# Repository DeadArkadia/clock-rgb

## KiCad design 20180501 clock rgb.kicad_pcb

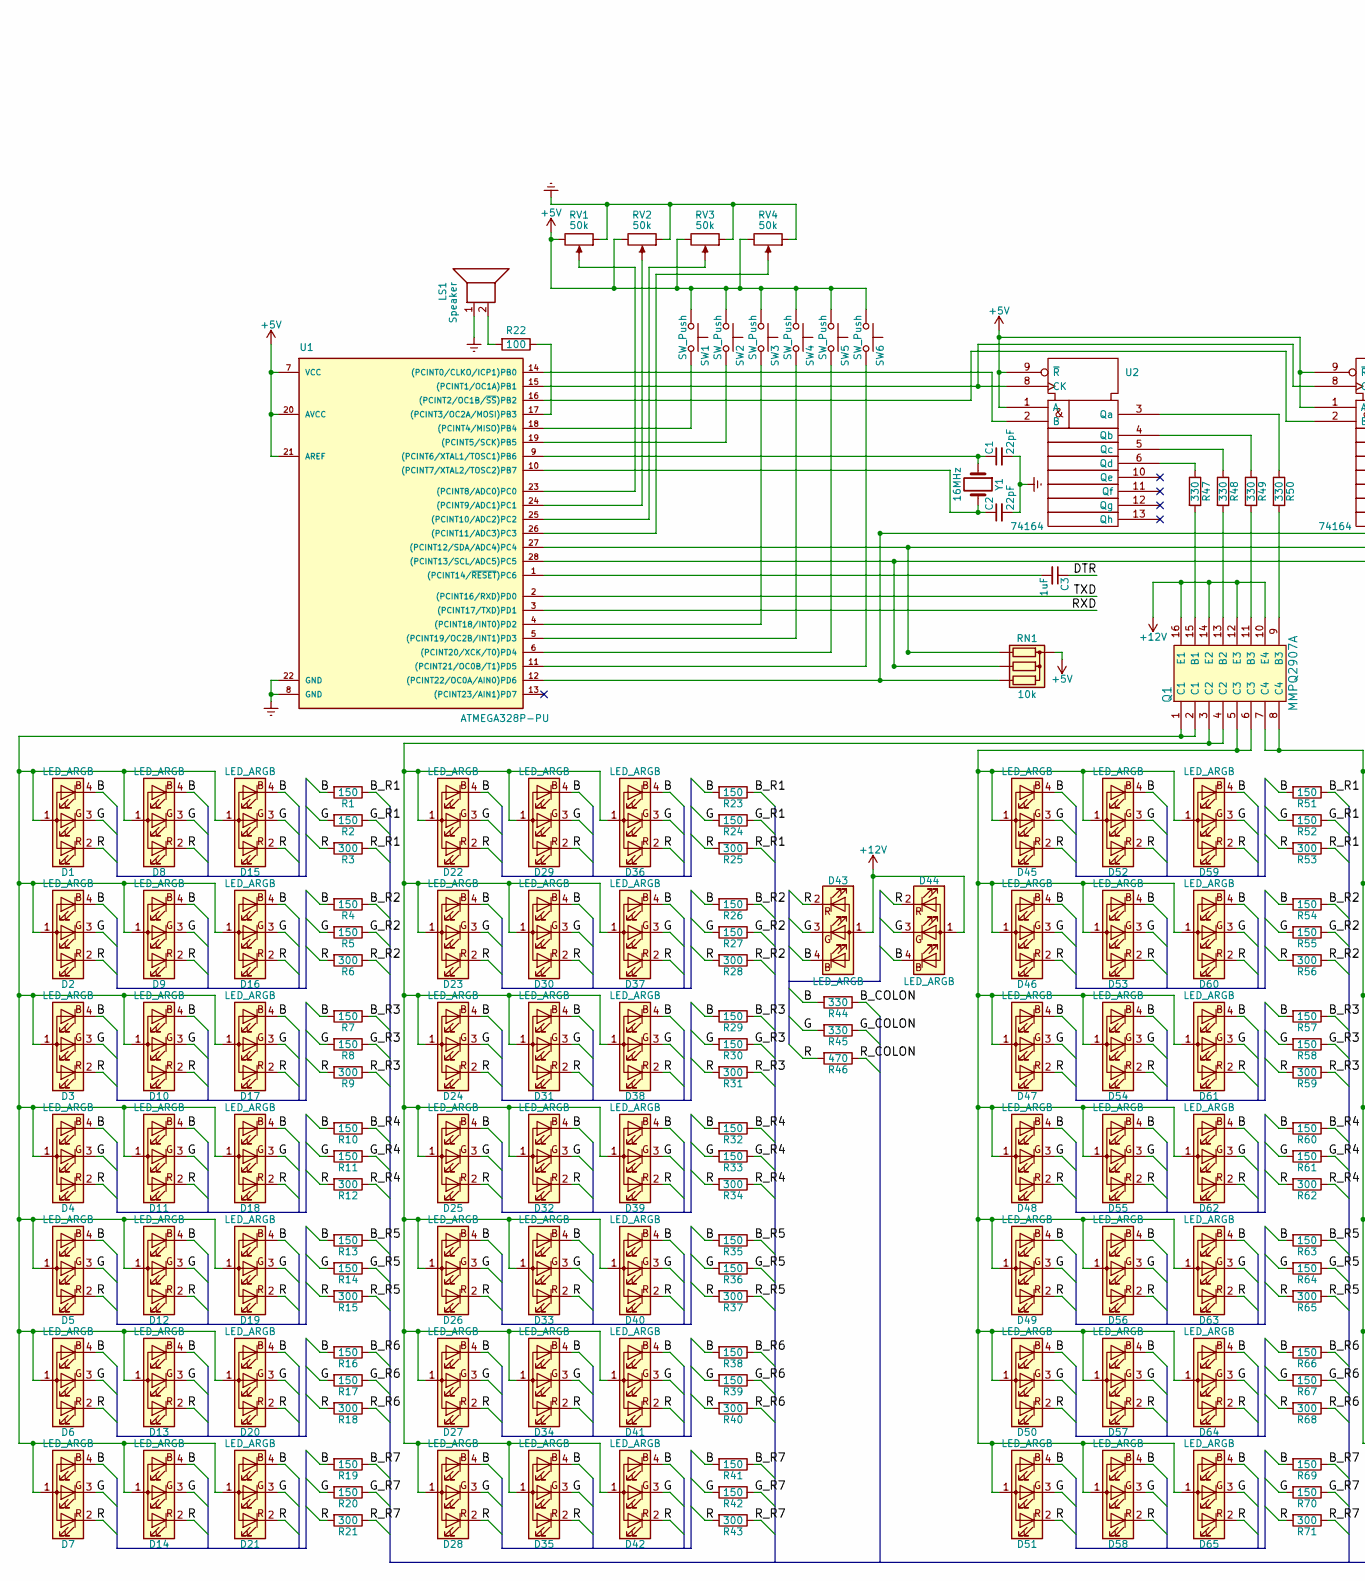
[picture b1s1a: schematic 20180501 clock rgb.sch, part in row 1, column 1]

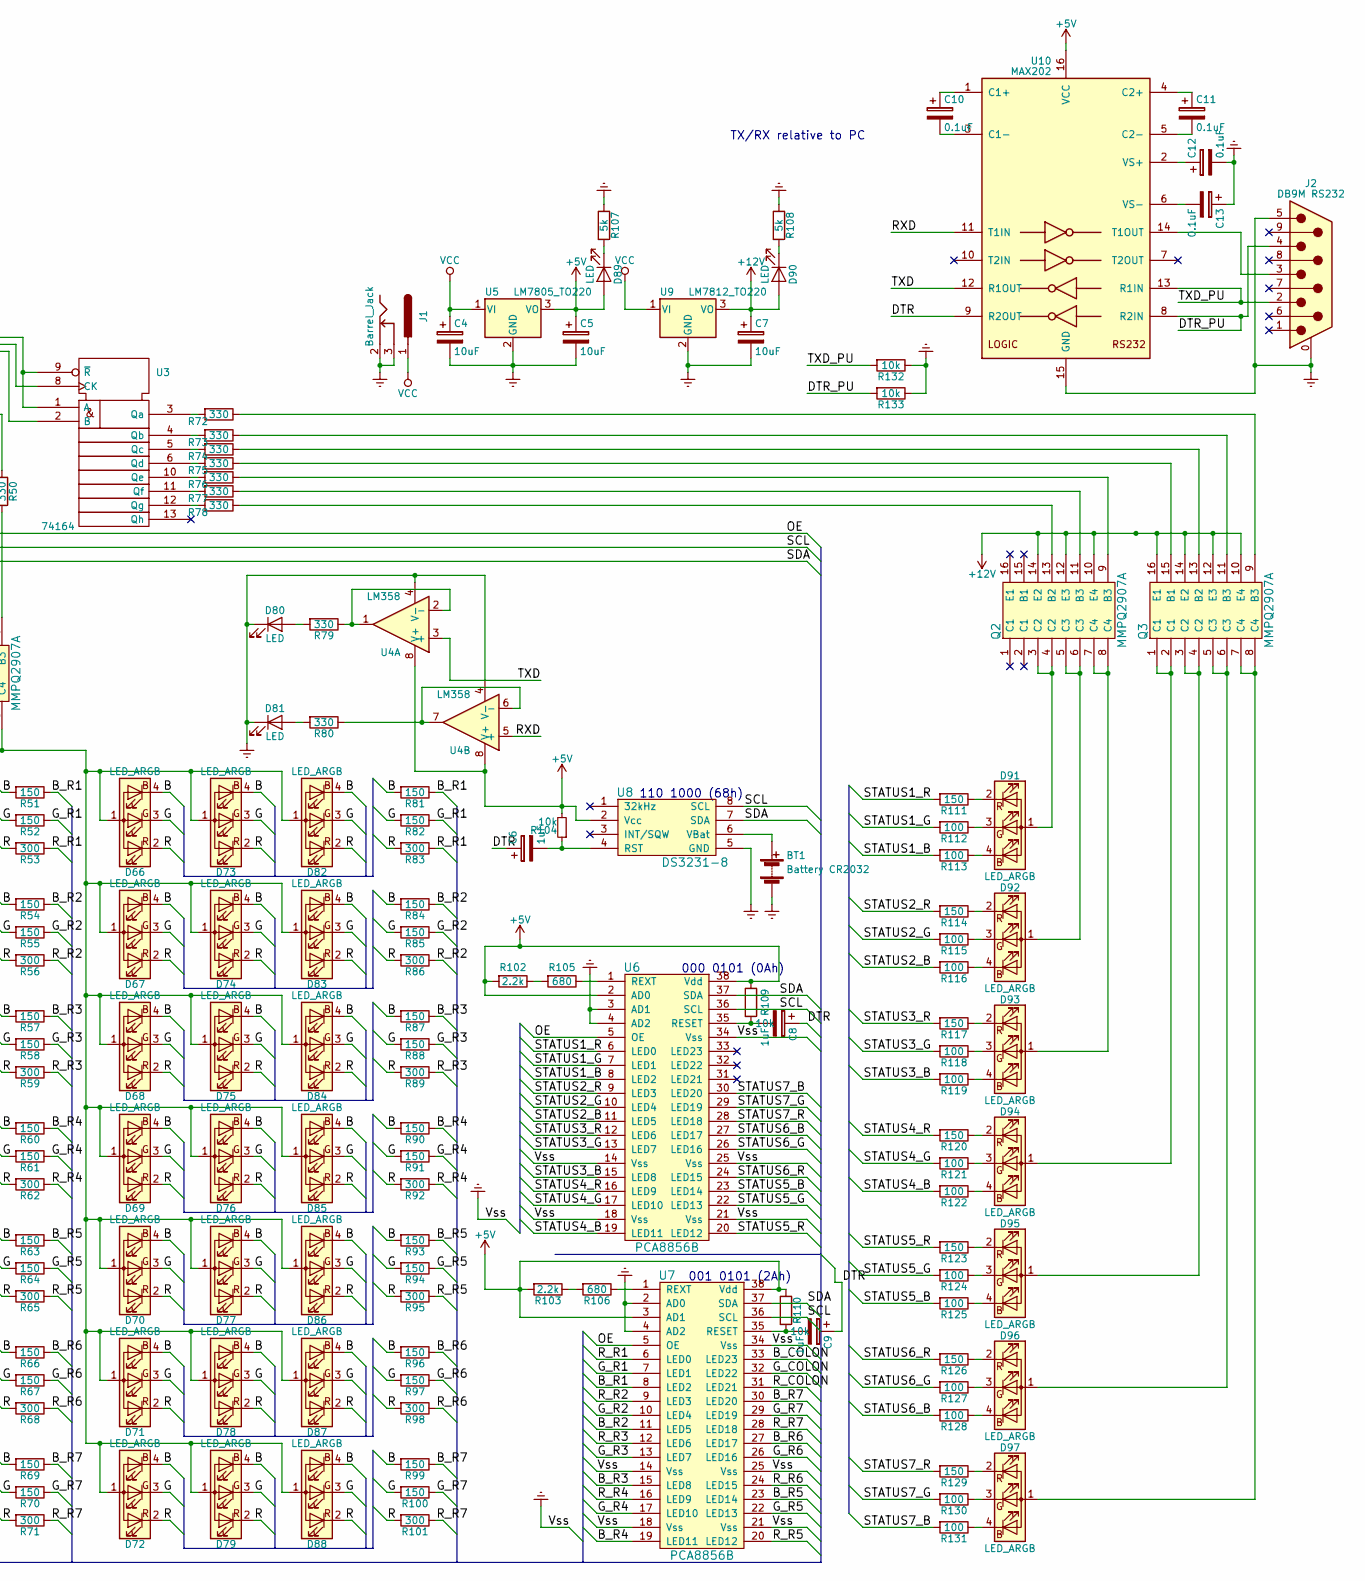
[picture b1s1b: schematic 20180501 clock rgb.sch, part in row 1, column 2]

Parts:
BT1: Battery CR2032; BatteryHolder_Keystone_1058_1x2032
C1, C2: 22pF; C_Rect_L4.0mm_W2.5mm_P2.50mm
C3: 1uF; C_Rect_L4.0mm_W2.5mm_P2.50mm
C4, C5, C7: 10uF; CP_Radial_D5.0mm_P2.50mm
C6, C8, C9: 1uF; CP_Radial_D5.0mm_P2.50mm
C10, C11, C12, C13: 0.1uF; CP_Radial_D5.0mm_P2.50mm
D1, D2, D3, D4, D5, D6, D7, D8, D9, D10, D11, D12, D13, D14, D15, D16, D17, D18, D19, D20, D21, D22, D23, D24, D25, D26, D27, D28, D29, D30, D31, D32, D33, D34, D35, D36, D37, D38, D39, D40, D41, D42, D43, D44, D45, D46, D47, D48, D49, D50, D51, D52, D53, D54, D55, D56, D57, D58, D59, D60, D61, D62, D63, D64, D65, D66, D67, D68, D69, D70, D71, D72, D73, D74, D75, D76, D77, D78, D79, D82, D83, D84, D85, D86, D87, D88, D91, D92, D93, D94, D95, D96, D97: LED_ARGB; LED_SK6812MINI_PLCC4_3.5x3.5mm_P1.75mm
D80, D81, D89, D90: LED; LED_D5.0mm
J1: Barrel_Jack; BARREL_JACK
J2: DB9M RS232; DSUB-9_Male_Horizontal_P2.77x2.84mm_EdgePinOffset7.70mm_Hou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
LS1: Speaker; Buzzer_15x7.5RM7.6
Q1, Q2, Q3: MMPQ2907A; SOIC-16_3.9x9.9mm_Pitch1.27mm
R1, R2, R4, R5, R7, R8, R10, R11, R13, R14, R16, R17, R19, R20, R23, R24, R26, R27, R29, R30, R32, R33, R35, R36, R38, R39, R41, R42, R51, R52, R54, R55, R57, R58, R60, R61, R63, R64, R66, R67, R69, R70, R81, R82, R84, R85, R87, R88, R90, R91, R93, R94, R96, R97, R99, R100, R111, R114, R117, R120, R123, R126, R129: 150; R_1210_3225Metric_Pad1.39x2.70mm_HandSolder
R3, R6, R9, R12, R15, R18, R21, R25, R28, R31, R34, R37, R40, R43, R53, R56, R59, R62, R65, R68, R71, R83, R86, R89, R92, R95, R98, R101: 300; R_1210_3225Metric_Pad1.39x2.70mm_HandSolder
R22: 100; R_Axial_DIN0207_L6.3mm_D2.5mm_P10.16mm_Horizontal
R44, R45, R47, R48, R49, R50, R72, R73, R74, R75, R76, R77, R78, R79, R80: 330; R_1210_3225Metric_Pad1.39x2.70mm_HandSolder
R46: 470; R_1210_3225Metric_Pad1.39x2.70mm_HandSolder
R102, R103: 2.2k; R_Axial_DIN0207_L6.3mm_D2.5mm_P10.16mm_Horizontal
R104: 10k; R_Axial_DIN0207_L6.3mm_D2.5mm_P10.16mm_Horizontal
R105, R106: 680; R_Axial_DIN0207_L6.3mm_D2.5mm_P10.16mm_Horizontal
R107, R108: 5k; R_Axial_DIN0207_L6.3mm_D2.5mm_P10.16mm_Horizontal
R109, R110, R132, R133: 10k; R_1210_3225Metric_Pad1.39x2.70mm_HandSolder
R112, R113, R115, R116, R118, R119, R121, R122, R124, R125, R127, R128, R130, R131: 100; R_1210_3225Metric_Pad1.39x2.70mm_HandSolder
RN1: 10k; R_Array_SIP4
RV1, RV2, RV3, RV4: 50k; Potentiometer_Alps_RK09K_Single_Vertical
SW1, SW2, SW3, SW4, SW5, SW6: SW_Push; SW_PUSH_6mm
U1: ATMEGA328P-PU; DIP-28_W7.62mm
U2, U3: 74164; DIP-14_W7.62mm
U4: LM358; SOIC-8_3.9x4.9mm_Pitch1.27mm
U5: LM7805_TO220; TO-220-3_Horizontal
U6, U7: PCA8856B; TSSOP-38_4.4x9.7mm_Pitch0.5mm
U8: DS3231-8; SOIC-8_3.9x4.9mm_Pitch1.27mm
U9: LM7812_TO220; TO-220-3_Horizontal
U10: MAX202; SOIC-16_3.9x9.9mm_Pitch1.27mm
Y1: 16MHz; Crystal_HC49-4H_Vertical

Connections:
+5V: C5.1, D89.2 (A), R102.2, R103.2, R104.2, R109.1, R110.1, RN1.1 (common), RV1.3, RV2.3, RV3.3, RV4.3, SW1.1, SW2.1, SW3.1, SW4.1, SW5.1, SW6.1, U1.7 (VCC), U1.20 (AVCC), U1.21 (AREF), U2.1 (A), U2.9 (~R), U3.1 (A), U3.9 (~R), U4.8 (V+), U5.3 (VO), U6.2 (AD0), U6.38 (Vdd), U7.3 (AD1), U7.38 (Vdd), U8.2 (Vcc), U10.16 (VCC)
+12V: C7.1, D43.1 (A), D44.1 (A), D90.2 (A), Q1.10 (E4), Q1.12 (E3), Q1.14 (E2), Q1.16 (E1), Q2.10 (E4), Q2.12 (E3), Q2.14 (E2), Q3.10 (E4), Q3.12 (E3), Q3.14 (E2), Q3.16 (E1), U9.3 (VO)
/B: D1.4 (BK), D2.4 (BK), D3.4 (BK), D4.4 (BK), D5.4 (BK), D6.4 (BK), D7.4 (BK), D8.4 (BK), D9.4 (BK), D10.4 (BK), D11.4 (BK), D12.4 (BK), D13.4 (BK), D14.4 (BK), D15.4 (BK), D16.4 (BK), D17.4 (BK), D18.4 (BK), D19.4 (BK), D20.4 (BK), D21.4 (BK), D22.4 (BK), D23.4 (BK), D24.4 (BK), D25.4 (BK), D26.4 (BK), D27.4 (BK), D28.4 (BK), D29.4 (BK), D30.4 (BK), D31.4 (BK), D32.4 (BK), D33.4 (BK), D34.4 (BK), D35.4 (BK), D36.4 (BK), D37.4 (BK), D38.4 (BK), D39.4 (BK), D40.4 (BK), D41.4 (BK), D42.4 (BK), D43.4 (BK), D44.4 (BK), D45.4 (BK), D46.4 (BK), D47.4 (BK), D48.4 (BK), D49.4 (BK), D50.4 (BK), D51.4 (BK), D52.4 (BK), D53.4 (BK), D54.4 (BK), D55.4 (BK), D56.4 (BK), D57.4 (BK), D58.4 (BK), D59.4 (BK), D60.4 (BK), D61.4 (BK), D62.4 (BK), D63.4 (BK), D64.4 (BK), D65.4 (BK), D66.4 (BK), D67.4 (BK), D68.4 (BK), D69.4 (BK), D70.4 (BK), D71.4 (BK), D72.4 (BK), D73.4 (BK), D74.4 (BK), D75.4 (BK), D76.4 (BK), D77.4 (BK), D78.4 (BK), D79.4 (BK), D82.4 (BK), D83.4 (BK), D84.4 (BK), D85.4 (BK), D86.4 (BK), D87.4 (BK), D88.4 (BK), R1.2, R4.2, R7.2, R10.2, R13.2, R16.2, R19.2, R23.2, R26.2, R29.2, R32.2, R35.2, R38.2, R41.2, R44.2, R51.2, R54.2, R57.2, R60.2, R63.2, R66.2, R69.2, R81.2, R84.2, R87.2, R90.2, R93.2, R96.2, R99.2
/B_COLON: R44.1, U7.33 (LED23)
/B_R1: R1.1, R23.1, R51.1, R81.1, U7.8 (LED2)
/B_R2: R4.1, R26.1, R54.1, R84.1, U7.11 (LED5)
/B_R3: R7.1, R29.1, R57.1, R87.1, U7.15 (LED8)
/B_R4: R10.1, R32.1, R60.1, R90.1, U7.19 (LED11)
/B_R5: R13.1, R35.1, R63.1, R93.1, U7.23 (LED14)
/B_R6: R16.1, R38.1, R66.1, R96.1, U7.27 (LED17)
/B_R7: R19.1, R41.1, R69.1, R99.1, U7.30 (LED20)
/DTR: C3.1, C6.1, C8.1, C9.1, U10.9 (R2OUT)
/DTR_PU: J2.4, R133.2, U10.8 (R2IN)
/G: D1.3 (GK), D2.3 (GK), D3.3 (GK), D4.3 (GK), D5.3 (GK), D6.3 (GK), D7.3 (GK), D8.3 (GK), D9.3 (GK), D10.3 (GK), D11.3 (GK), D12.3 (GK), D13.3 (GK), D14.3 (GK), D15.3 (GK), D16.3 (GK), D17.3 (GK), D18.3 (GK), D19.3 (GK), D20.3 (GK), D21.3 (GK), D22.3 (GK), D23.3 (GK), D24.3 (GK), D25.3 (GK), D26.3 (GK), D27.3 (GK), D28.3 (GK), D29.3 (GK), D30.3 (GK), D31.3 (GK), D32.3 (GK), D33.3 (GK), D34.3 (GK), D35.3 (GK), D36.3 (GK), D37.3 (GK), D38.3 (GK), D39.3 (GK), D40.3 (GK), D41.3 (GK), D42.3 (GK), D43.3 (GK), D44.3 (GK), D45.3 (GK), D46.3 (GK), D47.3 (GK), D48.3 (GK), D49.3 (GK), D50.3 (GK), D51.3 (GK), D52.3 (GK), D53.3 (GK), D54.3 (GK), D55.3 (GK), D56.3 (GK), D57.3 (GK), D58.3 (GK), D59.3 (GK), D60.3 (GK), D61.3 (GK), D62.3 (GK), D63.3 (GK), D64.3 (GK), D65.3 (GK), D66.3 (GK), D67.3 (GK), D68.3 (GK), D69.3 (GK), D70.3 (GK), D71.3 (GK), D72.3 (GK), D73.3 (GK), D74.3 (GK), D75.3 (GK), D76.3 (GK), D77.3 (GK), D78.3 (GK), D79.3 (GK), D82.3 (GK), D83.3 (GK), D84.3 (GK), D85.3 (GK), D86.3 (GK), D87.3 (GK), D88.3 (GK), R2.2, R5.2, R8.2, R11.2, R14.2, R17.2, R20.2, R24.2, R27.2, R30.2, R33.2, R36.2, R39.2, R42.2, R45.2, R52.2, R55.2, R58.2, R61.2, R64.2, R67.2, R70.2, R82.2, R85.2, R88.2, R91.2, R94.2, R97.2, R100.2
/G_COLON: R45.1, U7.32 (LED22)
/G_R1: R2.1, R24.1, R52.1, R82.1, U7.7 (LED1)
/G_R2: R5.1, R27.1, R55.1, R85.1, U7.10 (LED4)
/G_R3: R8.1, R30.1, R58.1, R88.1, U7.13 (LED7)
/G_R4: R11.1, R33.1, R61.1, R91.1, U7.17 (LED10)
/G_R5: R14.1, R36.1, R64.1, R94.1, U7.22 (LED13)
/G_R6: R17.1, R39.1, R67.1, R97.1, U7.26 (LED16)
/G_R7: R20.1, R42.1, R70.1, R100.1, U7.29 (LED19)
/OE: RN1.4 (R3), U1.12 ((PCINT22/OC0A/AIN0)PD6), U6.5 (OE), U7.5 (OE)
/R: D1.2 (RK), D2.2 (RK), D3.2 (RK), D4.2 (RK), D5.2 (RK), D6.2 (RK), D7.2 (RK), D8.2 (RK), D9.2 (RK), D10.2 (RK), D11.2 (RK), D12.2 (RK), D13.2 (RK), D14.2 (RK), D15.2 (RK), D16.2 (RK), D17.2 (RK), D18.2 (RK), D19.2 (RK), D20.2 (RK), D21.2 (RK), D22.2 (RK), D23.2 (RK), D24.2 (RK), D25.2 (RK), D26.2 (RK), D27.2 (RK), D28.2 (RK), D29.2 (RK), D30.2 (RK), D31.2 (RK), D32.2 (RK), D33.2 (RK), D34.2 (RK), D35.2 (RK), D36.2 (RK), D37.2 (RK), D38.2 (RK), D39.2 (RK), D40.2 (RK), D41.2 (RK), D42.2 (RK), D43.2 (RK), D44.2 (RK), D45.2 (RK), D46.2 (RK), D47.2 (RK), D48.2 (RK), D49.2 (RK), D50.2 (RK), D51.2 (RK), D52.2 (RK), D53.2 (RK), D54.2 (RK), D55.2 (RK), D56.2 (RK), D57.2 (RK), D58.2 (RK), D59.2 (RK), D60.2 (RK), D61.2 (RK), D62.2 (RK), D63.2 (RK), D64.2 (RK), D65.2 (RK), D66.2 (RK), D67.2 (RK), D68.2 (RK), D69.2 (RK), D70.2 (RK), D71.2 (RK), D72.2 (RK), D73.2 (RK), D74.2 (RK), D75.2 (RK), D76.2 (RK), D77.2 (RK), D78.2 (RK), D79.2 (RK), D82.2 (RK), D83.2 (RK), D84.2 (RK), D85.2 (RK), D86.2 (RK), D87.2 (RK), D88.2 (RK), R3.2, R6.2, R9.2, R12.2, R15.2, R18.2, R21.2, R25.2, R28.2, R31.2, R34.2, R37.2, R40.2, R43.2, R46.2, R53.2, R56.2, R59.2, R62.2, R65.2, R68.2, R71.2, R83.2, R86.2, R89.2, R92.2, R95.2, R98.2, R101.2
/RXD: U1.3 ((PCINT17/TXD)PD1), U4.5 (+), U10.11 (T1IN)
/R_COLON: R46.1, U7.31 (LED21)
/R_R1: R3.1, R25.1, R53.1, R83.1, U7.6 (LED0)
/R_R2: R6.1, R28.1, R56.1, R86.1, U7.9 (LED3)
/R_R3: R9.1, R31.1, R59.1, R89.1, U7.12 (LED6)
/R_R4: R12.1, R34.1, R62.1, R92.1, U7.16 (LED9)
/R_R5: R15.1, R37.1, R65.1, R95.1, U7.20 (LED12)
/R_R6: R18.1, R40.1, R68.1, R98.1, U7.24 (LED15)
/R_R7: R21.1, R43.1, R71.1, R101.1, U7.28 (LED18)
/SCL: RN1.2 (R1), U1.27 ((PCINT12/SDA/ADC4)PC4), U6.36 (SCL), U7.36 (SCL), U8.8 (SCL)
/SDA: RN1.3 (R2), U1.28 ((PCINT13/SCL/ADC5)PC5), U6.37 (SDA), U7.37 (SDA), U8.7 (SDA)
/STATUS1_B: R113.2, U6.8 (LED2)
/STATUS1_G: R112.2, U6.7 (LED1)
/STATUS1_R: R111.2, U6.6 (LED0)
/STATUS2_B: R116.2, U6.11 (LED5)
/STATUS2_G: R115.2, U6.10 (LED4)
/STATUS2_R: R114.2, U6.9 (LED3)
/STATUS3_B: R119.2, U6.15 (LED8)
/STATUS3_G: R118.2, U6.13 (LED7)
/STATUS3_R: R117.2, U6.12 (LED6)
/STATUS4_B: R122.2, U6.19 (LED11)
/STATUS4_G: R121.2, U6.17 (LED10)
/STATUS4_R: R120.2, U6.16 (LED9)
/STATUS5_B: R125.2, U6.23 (LED14)
/STATUS5_G: R124.2, U6.22 (LED13)
/STATUS5_R: R123.2, U6.20 (LED12)
/STATUS6_B: R128.2, U6.27 (LED17)
/STATUS6_G: R127.2, U6.26 (LED16)
/STATUS6_R: R126.2, U6.24 (LED15)
/STATUS7_B: R131.2, U6.30 (LED20)
/STATUS7_G: R130.2, U6.29 (LED19)
/STATUS7_R: R129.2, U6.28 (LED18)
/TXD: U1.2 ((PCINT16/RXD)PD0), U4.3 (+), U10.12 (R1OUT)
/TXD_PU: J2.2, R132.2, U10.13 (R1IN)
Earth: BT1.2 (-), C1.2, C2.2, C4.2, C5.2, C7.2, C12.2, C13.1, D80.1 (K), D81.1 (K), J1.2, J1.3, J2.0 (PAD), J2.5, LS1.1, R107.1, R108.1, R132.1, R133.1, RV1.1, RV2.1, RV3.1, RV4.1, U1.8 (GND), U1.22 (GND), U2.7 (Vss), U3.7 (Vss), U4.4 (V-), U5.2 (GND), U6.3 (AD1), U6.4 (AD2), U6.14 (Vss), U6.18 (Vss), U6.21 (Vss), U6.25 (Vss), U6.34 (Vss), U7.2 (AD0), U7.4 (AD2), U7.14 (Vss), U7.18 (Vss), U7.21 (Vss), U7.25 (Vss), U7.34 (Vss), U8.5 (GND), U9.2 (GND), U10.15 (GND)
unnamed: BT1.1 (+), U8.6 (VBat)
unnamed: C1.1, U1.9 ((PCINT6/XTAL1/TOSC1)PB6), Y1.1
unnamed: C2.1, U1.10 ((PCINT7/XTAL2/TOSC2)PB7), Y1.2
unnamed: C3.2, U1.1 ((PCINT14/~RESET~)PC6)
unnamed: C6.2, R104.1, U8.4 (RST)
unnamed: C8.2, R109.2, U6.35 (RESET)
unnamed: C9.2, R110.2, U7.35 (RESET)
unnamed: C10.1, U10.1 (C1+)
unnamed: C10.2, U10.3 (C1-)
unnamed: C11.1, U10.4 (C2+)
unnamed: C11.2, U10.5 (C2-)
unnamed: C12.1, U10.2 (VS+)
unnamed: C13.2, U10.6 (VS-)
unnamed: D1.1 (A), D2.1 (A), D3.1 (A), D4.1 (A), D5.1 (A), D6.1 (A), D7.1 (A), D8.1 (A), D9.1 (A), D10.1 (A), D11.1 (A), D12.1 (A), D13.1 (A), D14.1 (A), D15.1 (A), D16.1 (A), D17.1 (A), D18.1 (A), D19.1 (A), D20.1 (A), D21.1 (A), Q1.1 (C1), Q1.2 (C1)
unnamed: D22.1 (A), D23.1 (A), D24.1 (A), D25.1 (A), D26.1 (A), D27.1 (A), D28.1 (A), D29.1 (A), D30.1 (A), D31.1 (A), D32.1 (A), D33.1 (A), D34.1 (A), D35.1 (A), D36.1 (A), D37.1 (A), D38.1 (A), D39.1 (A), D40.1 (A), D41.1 (A), D42.1 (A), Q1.3 (C2), Q1.4 (C2)
unnamed: D45.1 (A), D46.1 (A), D47.1 (A), D48.1 (A), D49.1 (A), D50.1 (A), D51.1 (A), D52.1 (A), D53.1 (A), D54.1 (A), D55.1 (A), D56.1 (A), D57.1 (A), D58.1 (A), D59.1 (A), D60.1 (A), D61.1 (A), D62.1 (A), D63.1 (A), D64.1 (A), D65.1 (A), Q1.5 (C3), Q1.6 (C3)
unnamed: D66.1 (A), D67.1 (A), D68.1 (A), D69.1 (A), D70.1 (A), D71.1 (A), D72.1 (A), D73.1 (A), D74.1 (A), D75.1 (A), D76.1 (A), D77.1 (A), D78.1 (A), D79.1 (A), D82.1 (A), D83.1 (A), D84.1 (A), D85.1 (A), D86.1 (A), D87.1 (A), D88.1 (A), Q1.7 (C4), Q1.8 (C4)
unnamed: D80.2 (A), R79.2
unnamed: D81.2 (A), R80.2
unnamed: D89.1 (K), R107.2
unnamed: D90.1 (K), R108.2
unnamed: D91.1 (A), Q2.3 (C2), Q2.4 (C2)
unnamed: D91.2 (RK), R111.1
unnamed: D91.3 (GK), R112.1
unnamed: D91.4 (BK), R113.1
unnamed: D92.1 (A), Q2.5 (C3), Q2.6 (C3)
unnamed: D92.2 (RK), R114.1
unnamed: D92.3 (GK), R115.1
unnamed: D92.4 (BK), R116.1
unnamed: D93.1 (A), Q2.7 (C4), Q2.8 (C4)
unnamed: D93.2 (RK), R117.1
unnamed: D93.3 (GK), R118.1
unnamed: D93.4 (BK), R119.1
unnamed: D94.1 (A), Q3.1 (C1), Q3.2 (C1)
unnamed: D94.2 (RK), R120.1
unnamed: D94.3 (GK), R121.1
unnamed: D94.4 (BK), R122.1
unnamed: D95.1 (A), Q3.3 (C2), Q3.4 (C2)
unnamed: D95.2 (RK), R123.1
unnamed: D95.3 (GK), R124.1
unnamed: D95.4 (BK), R125.1
unnamed: D96.1 (A), Q3.5 (C3), Q3.6 (C3)
unnamed: D96.2 (RK), R126.1
unnamed: D96.3 (GK), R127.1
unnamed: D96.4 (BK), R128.1
unnamed: D97.1 (A), Q3.7 (C4), Q3.8 (C4)
unnamed: D97.2 (RK), R129.1
unnamed: D97.3 (GK), R130.1
unnamed: D97.4 (BK), R131.1
unnamed: J2.3, U10.14 (T1OUT)
unnamed: LS1.2, R22.2
unnamed: Q1.9 (B3), R50.2
unnamed: Q1.11 (B3), R49.2
unnamed: Q1.13 (B2), R48.2
unnamed: Q1.15 (B1), R47.2
unnamed: Q2.9 (B3), R76.1
unnamed: Q2.11 (B3), R77.1
unnamed: Q2.13 (B2), R78.1
unnamed: Q3.9 (B3), R72.1
unnamed: Q3.11 (B3), R73.1
unnamed: Q3.13 (B2), R74.1
unnamed: Q3.15 (B1), R75.1
unnamed: R22.1, U1.17 ((PCINT3/OC2A/MOSI)PB3)
unnamed: R47.1, U2.6 (Qd)
unnamed: R48.1, U2.5 (Qc)
unnamed: R49.1, U2.4 (Qb)
unnamed: R50.1, U2.3 (Qa)
unnamed: R72.2, U3.3 (Qa)
unnamed: R73.2, U3.4 (Qb)
unnamed: R74.2, U3.5 (Qc)
unnamed: R75.2, U3.6 (Qd)
unnamed: R76.2, U3.10 (Qe)
unnamed: R77.2, U3.11 (Qf)
unnamed: R78.2, U3.12 (Qg)
unnamed: R79.1, U4.1, U4.2 (-)
unnamed: R80.1, U4.6 (-), U4.7
unnamed: R102.1, R105.2
unnamed: R103.1, R106.2
unnamed: R105.1, U6.1 (REXT)
unnamed: R106.1, U7.1 (REXT)
unnamed: RV1.2, U1.23 ((PCINT8/ADC0)PC0)
unnamed: RV2.2, U1.24 ((PCINT9/ADC1)PC1)
unnamed: RV3.2, U1.25 ((PCINT10/ADC2)PC2)
unnamed: RV4.2, U1.26 ((PCINT11/ADC3)PC3)
unnamed: SW1.2, U1.18 ((PCINT4/MISO)PB4)
unnamed: SW2.2, U1.19 ((PCINT5/SCK)PB5)
unnamed: SW3.2, U1.4 ((PCINT18/INT0)PD2)
unnamed: SW4.2, U1.5 ((PCINT19/OC2B/INT1)PD3)
unnamed: SW5.2, U1.6 ((PCINT20/XCK/T0)PD4)
unnamed: SW6.2, U1.11 ((PCINT21/OC0B/T1)PD5)
unnamed: U1.14 ((PCINT0/CLKO/ICP1)PB0), U2.2 (B)
unnamed: U1.15 ((PCINT1/OC1A)PB1), U2.8 (CK), U3.8 (CK)
unnamed: U1.16 ((PCINT2/OC1B/~SS~)PB2), U3.2 (B)
VCC: C4.1, J1.1, U5.1 (VI), U9.1 (VI)
Vdd: U2.14 (Vdd), U3.14 (Vdd)

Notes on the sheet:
110 1000 (68h)
001 0101 (2Ah)
000 0101 (0Ah)
TX/RX relative to PC

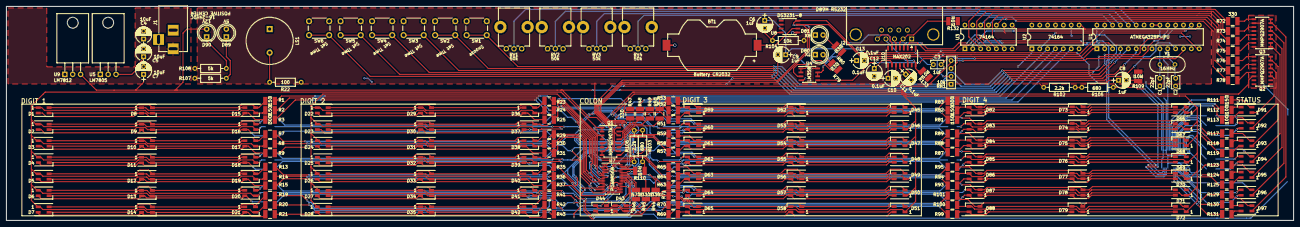
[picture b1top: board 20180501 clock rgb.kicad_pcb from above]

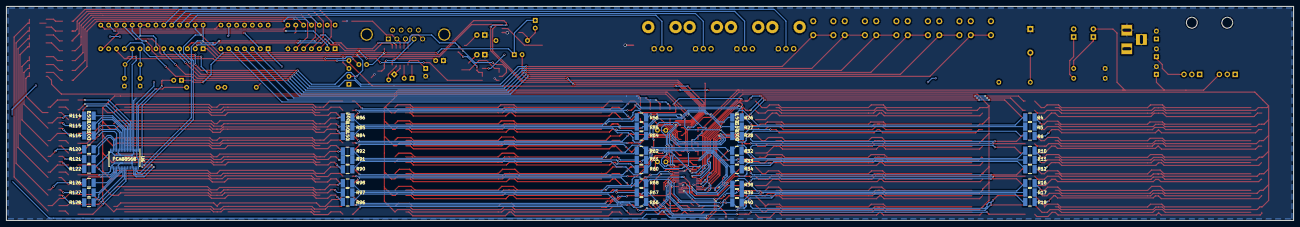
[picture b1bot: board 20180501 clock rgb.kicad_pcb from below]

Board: 2 copper layers, 415.0 x 69.0 mm, 272 parts (46 on the bottom side), 154 nets.

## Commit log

2018-05-07 resubmit to github
    this desktop app is dumb
2018-05-08 Serial port work
    Added MAX202 and supporting circuitry,
    Changed LM358 to a SOIC package
2018-05-09 created gerber files
    final, ready to send in to jlcpcb
2018-05-09 jesus github
    asdf
